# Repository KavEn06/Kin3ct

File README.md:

# Kin3ct

## What is it?
Kin3ct is a handheld 3D scanner built around a Kinect v2 sensor and a Raspberry Pi 5. It’s designed to let you scan objects and spaces while seeing the point cloud build live on the screen, instead of waiting to process photos later with photogrammetry. The scanner will have a built‑in 7‑inch touchscreen so you can watch the scan as you move, along with a few shortcut buttons on the side to start/stop scanning and switch modes.  
Right now, the plan is to capture the raw data on the Pi and clean it up later on a PC for use in CAD, Blender, or other 3D software.

## Backstory / Why did I build it?
I’ve always thought 3D scanners were super cool, but most of the good ones are either huge, expensive, or both. At first I looked into doing photogrammetry, but it felt too slow — I really wanted something that could show what I was scanning *live*, so you can see if you missed a spot or need to rescan right away. That’s when I thought about using a Kinect v2 with a Raspberry Pi to make a handheld scanner that’s (sort of) portable and way cheaper than commercial scanners. It probably won’t be as accurate or polished, but the idea of being able to walk around an object and watch the point cloud build up on a little screen sounded too fun not to try.

## Hardware
- **Raspberry Pi 5**             – handles running RTAB‑Map and collecting the data
- **Kinect v2 + USB adapter**    – the depth sensor that actually does the scanning
- **7-inch LCD touchscreen**     – to see the point cloud build live while scanning
- **NVMe SSD**                   – extra storage for saving larger scans without swapping SD cards
- **Custom 4-button PCB**        – for shortcut controls (start/stop scan, switch modes, etc.)
- **3D printed case**            – inspired by the Revopoint Miraco so it’s easier to hold with two hands

## 3D Model

If anyone wants to take a peek at the CAD model, here’s the [Onshape document link](https://cad.onshape.com/documents/48930f9beb6214e895f71f2e/w/9f4ed8c437f438cf09a60f4e/e/15fc98493092e56e2661dd14?renderMode=0&uiState=68891b22b66bb758b3d517d6).

## Schematic and PCB 

Interms of the wiring for the Kinect, it goes such as: 
Kinect -> Adapter -> Raspberry  5 
Power -> Adapter -> Raspberry Pi 5 and Kinect 

## Firmware 
For controlling the scanner, I made a small 4‑button PCB that connects directly to the GPIO pins on the Raspberry Pi.  
There will be a Python script running on the Pi can just watch for GPIO state changes and trigger the right RTAB‑Map commands or shortcut functions like:
- Start/stop scanning
- Switch scanning modes
- Reset/clear the current point cloud
- Maybe something else later on

For the actual scanning, I’m planning to run RTAB‑Map on the Raspberry Pi 5. RTAB‑Map is an open‑source SLAM (Simultaneous Localization and Mapping) library that can build a 3D point cloud *live while scanning*, which is exactly what I wanted from the start.

To get the Kinect v2 data into RTAB‑Map, I’ll be using libfreenect2 — an open‑source driver that lets Linux talk to the Kinect v2 over USB 3.  
There isn’t an official ARM build, but it *does* work on the Pi if you build it from source (thanks to the Pi 5’s faster CPU and USB 3.0 ports).

I’m mostly following this guide on Instructables:  
👉 [RGB‑D SLAM With Kinect on Raspberry Pi 4 (Buster / ROS)](https://www.instructables.com/RGB-D-SLAM-With-Kinect-on-Raspberry-Pi-4-Buster-RO/)  

The general plan:
- Build and install libfreenect2 on the Pi so the Kinect v2 can stream depth + RGB data  
- Set up RTAB‑Map (through ROS) to receive that data and do live SLAM
- Save the generated point clouds to the SSD for cleanup later on the PC

This way, the Pi handles the live scanning part, and I can do heavier mesh cleanup or conversions in Blender or MeshLab afterward.  

### BOM 
| Item                        | Purpose                       | Source | Price |
|----------------------------|------------------------------|-------|------:|
| Raspberry Pi 5             | Main compute unit            | [PiShop](https://www.pishop.ca/product/raspberry-pi-4-model-b-4gb/) | $84 |
| 7 inch LCD Display + Touch | Display & user interface     | [AliExpress](https://www.aliexpress.com/item/1005006420023450.html?invitationCode=MWVGaWdsZDc0cUZBdVBDM3l3bnY2ZGI4ckF6NFl1RjcwaTVFclZqZytLU2VQemFTZUJrNWVWT0s1MU1hdTAyWg&srcSns=sns_Copy&spreadType=socialShare&social_params=21892192294&bizType=ProductDetail&spreadCode=MWVGaWdsZDc0cUZBdVBDM3l3bnY2ZGI4ckF6NFl1RjcwaTVFclZqZytLU2VQemFTZUJrNWVWT0s1MU1hdTAyWg&aff_fcid=bc58928340ae4fef85f7e64e18bd7d7a-1753674064912-08252-_mPIB3Jt&tt=MG&aff_fsk=_mPIB3Jt&aff_platform=default&sk=_mPIB3Jt&aff_trace_key=bc58928340ae4fef85f7e64e18bd7d7a-1753674064912-08252-_mPIB3Jt&shareId=21892192294&businessType=ProductDetail&platform=AE&terminal_id=f0c0659a4ca447babbee09709f77824e&afSmartRedirect=y) | $40 |
| Kinect v2 + Adapter        | Depth camera for scanning    | Owned | $45 |
| Push Button                | Physical controls (start/stop etc.) | [AliExpress](https://www.aliexpress.com/item/32815969627.html?invitationCode=MWVGaWdsZDc0cUZ3UlZKTHg5WXhOZGI4ckF6NFl1RjcwaTVFclZqZytLU2VQemFTZUJrNWVWT0s1MU1hdTAyWg&srcSns=sns_Copy&spreadType=socialShare&social_params=21887243335&bizType=ProductDetail&spreadCode=MWVGaWdsZDc0cUZ3UlZKTHg5WXhOZGI4ckF6NFl1RjcwaTVFclZqZytLU2VQemFTZUJrNWVWT0s1MU1hdTAyWg&aff_fcid=4c7a59c12cce419489546f7f6a67c5eb-1753674154916-06773-_mMydiq7&tt=MG&aff_fsk=_mMydiq7&aff_platform=default&sk=_mMydiq7&aff_trace_key=4c7a59c12cce419489546f7f6a67c5eb-1753674154916-06773-_mMydiq7&shareId=21887243335&businessType=ProductDetail&platform=AE&terminal_id=f0c0659a4ca447babbee09709f77824e&afSmartRedirect=y) | $2 |
| Custom PCB                 | Connects buttons, SSD, etc.  | JLCPCB | $5 |
| 3D Printed Case            | Holds everything together    | Self-Sourced | $0 |
| NVMe SSD                   | Storage for scan data        | Owned | $0 |
|                            |                              |Total CAD | $177 |
|                            |                              |Total USD | $128 |

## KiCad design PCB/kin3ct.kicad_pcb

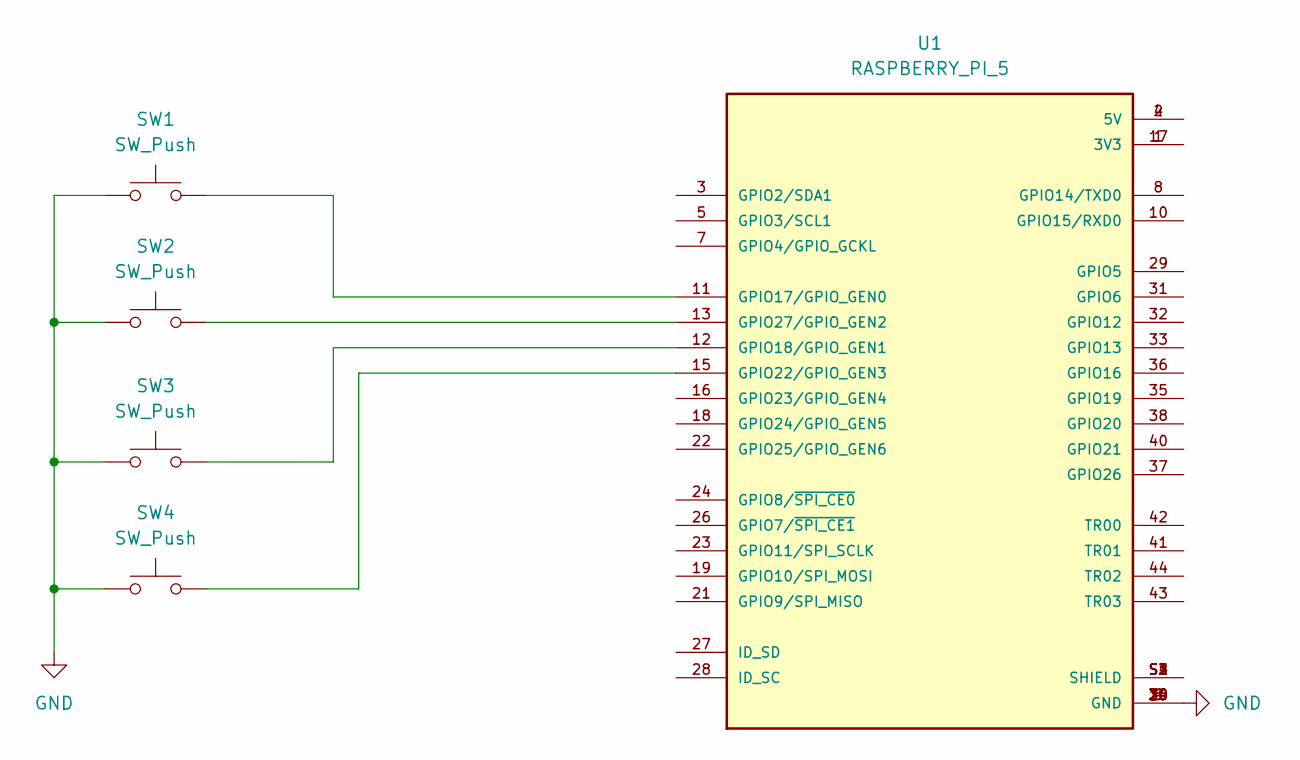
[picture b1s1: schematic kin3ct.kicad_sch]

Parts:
SW1, SW2, SW3, SW4: SW_Push; SW_PUSH_6mm_H4.3mm
U1: RASPBERRY_PI_5; MODULE_RASPBERRY_PI_4_MODEL_B_8G; PARTREV 4

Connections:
GND: SW1.1, SW2.1, SW3.1, SW4.1, U1.6 (GND), U1.9 (GND), U1.14 (GND), U1.20 (GND), U1.25 (GND), U1.30 (GND), U1.34 (GND), U1.39 (GND)
unnamed: U1.1 (3V3), U1.17 (3V3)
unnamed: U1.2 (5V), U1.4 (5V)
unnamed: SW1.2, U1.11 (GPIO17/GPIO_GEN0)
unnamed: SW3.2, U1.12 (GPIO18/GPIO_GEN1)
unnamed: SW4.2, U1.15 (GPIO22/GPIO_GEN3)
unnamed: SW2.2, U1.13 (GPIO27/GPIO_GEN2)
unnamed: U1.S1 (SHIELD), U1.S2 (SHIELD), U1.S3 (SHIELD), U1.S4 (SHIELD)

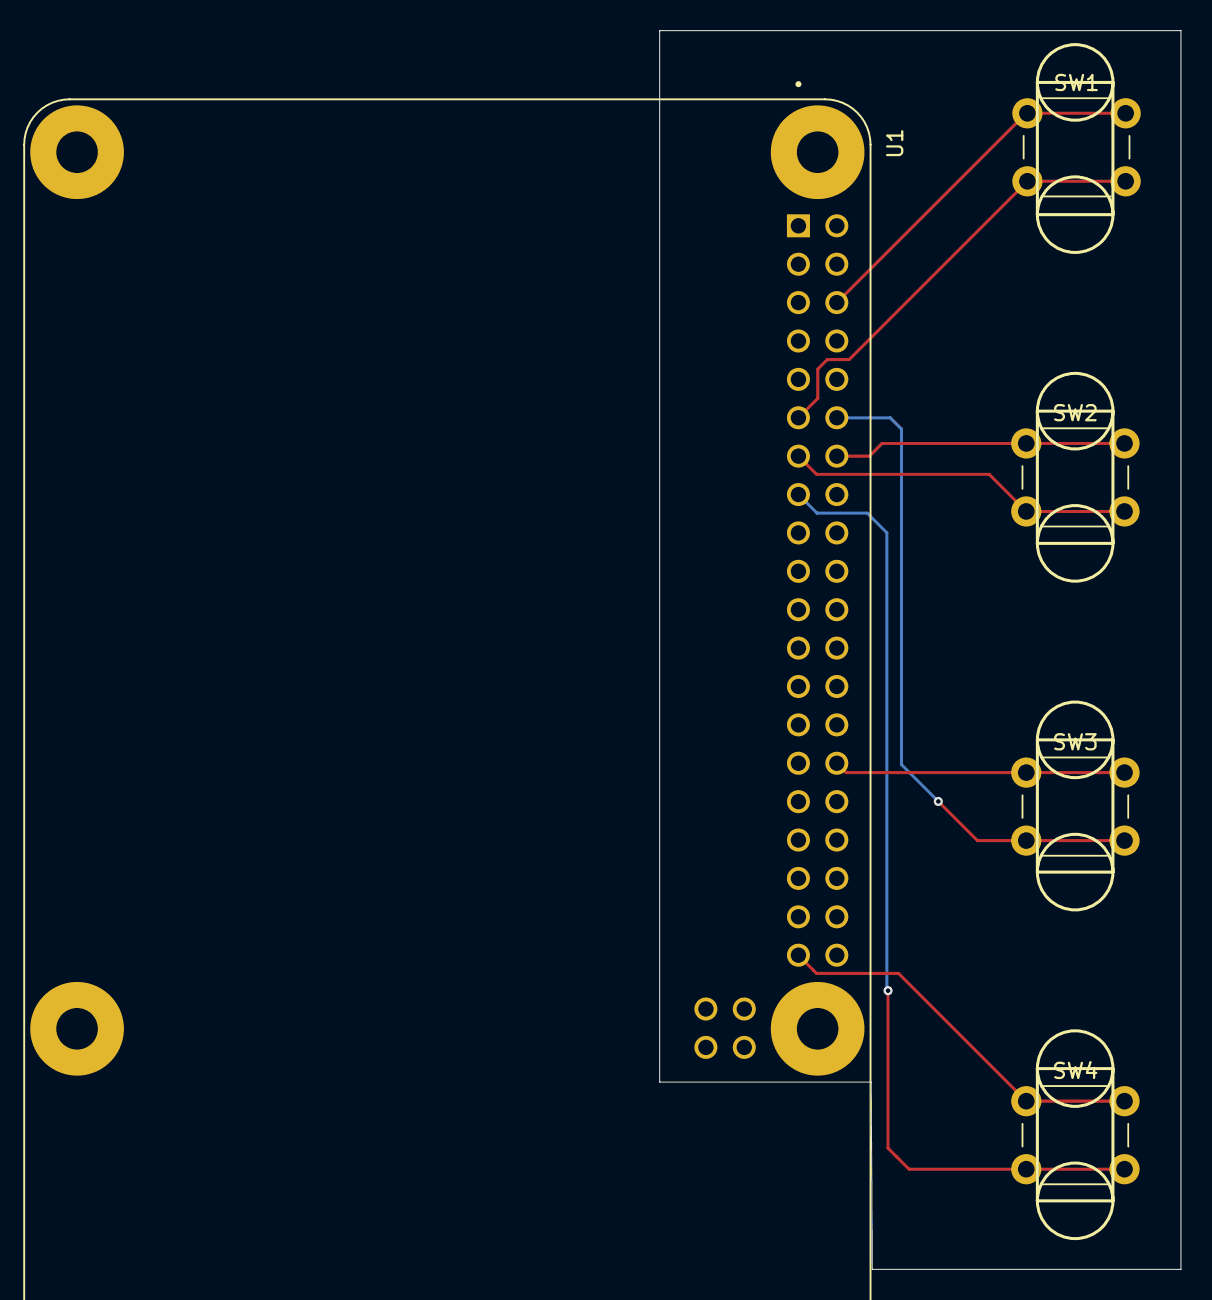
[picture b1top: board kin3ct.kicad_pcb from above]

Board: 2 copper layers, 34.5 x 82.0 mm, 5 parts (0 on the bottom side), 8 nets.

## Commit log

2025-07-29 Create a
2025-07-29 cad files
2025-07-29 pcb files
